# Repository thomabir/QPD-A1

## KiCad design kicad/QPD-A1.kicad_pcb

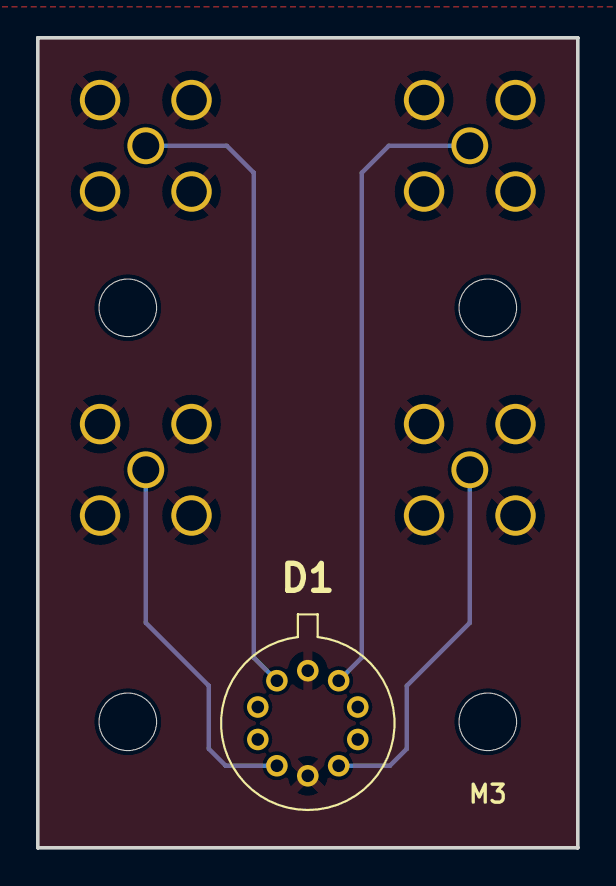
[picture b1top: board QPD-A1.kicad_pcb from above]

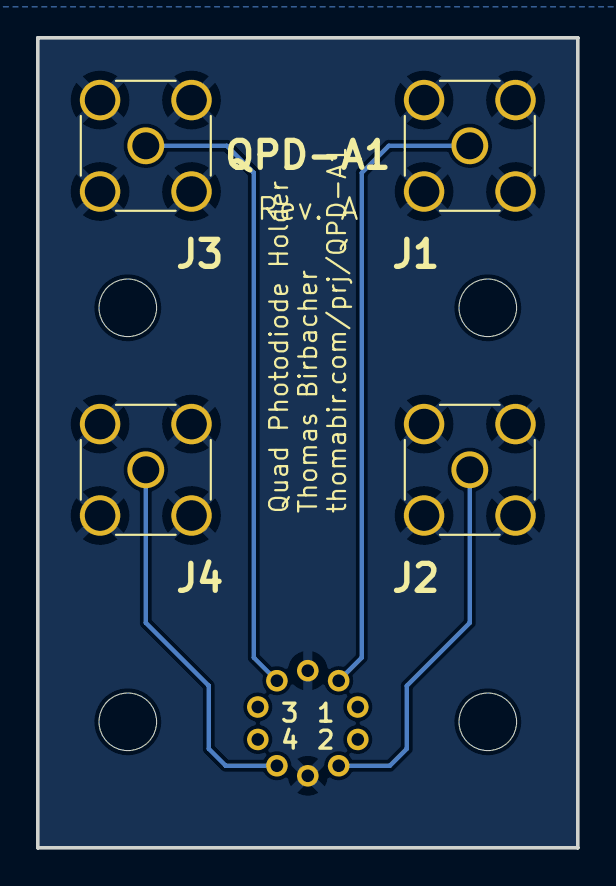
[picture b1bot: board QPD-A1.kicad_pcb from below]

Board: 2 copper layers, 30.0 x 45.0 mm, 9 parts (4 on the bottom side), 5 nets.

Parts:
D1: quadrant_photodiode; TO-5-10 S4349
H1, H2, H3, H4: MountingHole; MountingHole_3.2mm_M3_DIN965
J1, J2, J3, J4: Amphenol 132134; SMA_Amphenol_132291_Vertical

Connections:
/SIG_A: D1.4 (Anode_A), J4.1
/SIG_B: D1.6 (Anode_B), J2.1
/SIG_C: D1.9 (Anode_C), J1.1
/SIG_D: D1.1 (Anode_D), J3.1
GND: D1.5 (Cathode), D1.10 (Cathode), J1.2, J2.2, J3.2, J4.2

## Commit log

2023-04-04 Add kicad files
2023-04-04 Add LICENSE
2023-05-17 Change trace spacing a bit
